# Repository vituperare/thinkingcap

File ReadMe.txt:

The Thinking Cap v1.0 is the first major release of Grindhouse Wet Wares' implementation of the 
tDCS (transcranial Direct Current Stimulation and CES (Cranial Electrotherapy Stimulation)
concepts.  The idea is to stimulate your brain with direct current (in the case of tDCS)
or with square waves of current (in the case of CES) which can either raise or lower the
potential energy of the stimulated neurons, depending on the orientation of electrodes.
This allows them to fire more or less easily, and activates or deactivates a given region,
thus engaging certain brain states.

The code (included) is programmed to control an Arduino-compatible microcontroller to deliver
the necessary current.  It comes in the form of a library, so the hacker can choose his way of
controlling the current.  To create an instantiation of the ThinkingCap class, simply call the
"ThinkingCap" constructor, and then call the methods corresponding to the desired action.

The tDCS setting uses a current source and PWM to ramp up the current at the beginning, and ramp
it back down after a given stimulation time (20 minutes by default, but this setting is also
changeable).  The CES setting pulls a constant square wave, with a frequency to be set by the
user.

If the component values from the schematic are used, the current pulled should be roughly 0.5 mA
or less, but by changing these values, the current level can be manipulated.  However, pulling
currents in excess of 2 mA is not recommended for any use.

The "software" folder contains the software necessary to control the Thinking Cap.  This consists
in an Arduino library called "thinkingcap" and a sample Arduino sketch called "TCexample.ino" that
imports this library.  The example code is designed to apply CES or tDCS depending on the position
of a switch, and to begin when a push-button is activated.

THe "hardware" folder contains gerber files, a bill of materials, and Eagle files necessary to create
a PCB for the Thinking Cap.  This is included within the "thinkingcap10a" folder; the "thinkingcap10b"
folder contains a design for a separate circuit that is not released nor recommended for use.

Thinking Cap v1.0 designed by ianmathwiz7; released 7-1-2013 by Grindhouse Wetware..

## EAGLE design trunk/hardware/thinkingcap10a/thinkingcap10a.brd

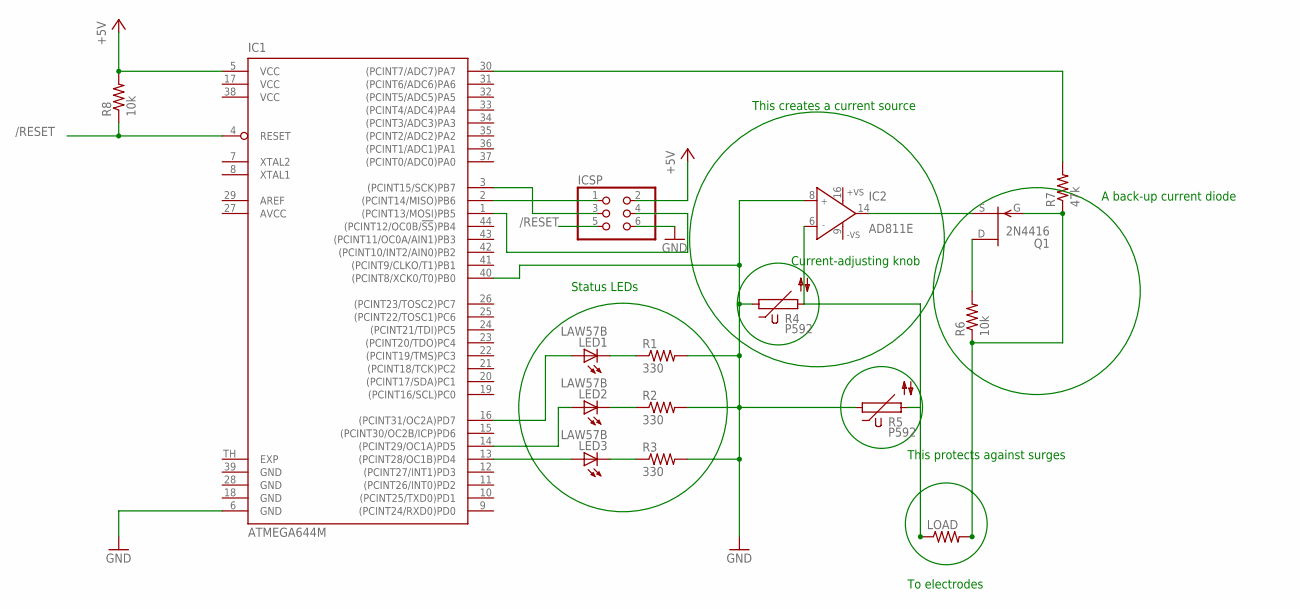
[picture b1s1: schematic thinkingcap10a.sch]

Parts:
IC1: ATMEGA644M; MLF44-TH
IC2: AD811E; PLCC20
ICSP: PINHD-2X3/90; 2X03/90
LED1, LED2, LED3: LAW57B; W57B
LOAD: R-US_0204/2V; 0204V
Q1: 2N4416; TO72
R1, R2, R3: 330; 0204V
R4, R5: P592
R6, R8: 10k; 0204V
R7: 47k; 0204V

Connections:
+5V: IC1.5 (VCC), ICSP.2, R8.2
/RESET: IC1.4 (RESET), ICSP.5, R8.1
AVCC: IC1.27 (AVCC)
EXP: IC1.TH (EXP)
GND: IC1.6 (GND), IC1.18 (GND), IC1.28 (GND), IC1.39 (GND), IC1.40 ((PCINT8/XCK0/T0)PB0), IC2.8 (IN+), ICSP.6, R1.2, R2.2, R3.2
unnamed: IC1.13 ((PCINT28/OC1B)PD4), LED3.A
unnamed: IC1.14 ((PCINT29/OC1A)PD5), LED2.A
unnamed: IC1.16 ((PCINT31/OC2A)PD7), LED1.A
unnamed: LED1.C, LED1.C@1 (C), LED1.C@2 (C), LED1.C@3 (C), LED1.C@4 (C), LED1.C@5 (C), R1.1
unnamed: LED2.C, LED2.C@1 (C), LED2.C@2 (C), LED2.C@3 (C), LED2.C@4 (C), LED2.C@5 (C), R2.1
unnamed: LED3.C, LED3.C@1 (C), LED3.C@2 (C), LED3.C@3 (C), LED3.C@4 (C), LED3.C@5 (C), R3.1
unnamed: IC1.2 ((PCINT14/MISO)PB6), ICSP.1
unnamed: IC2.6 (IN-), LOAD.1
unnamed: IC2.14 (OUT), Q1.1 (S)
unnamed: Q1.2 (D), R6.2
unnamed: IC1.30 ((PCINT7/ADC7)PA7), R7.2
unnamed: LOAD.2, Q1.3 (G), R6.1, R7.1
unnamed: IC1.3 ((PCINT15/SCK)PB7), ICSP.3
unnamed: IC1.1 ((PCINT13/MOSI)PB5), ICSP.4
VCC: IC1.17 (VCC), IC1.38 (VCC)

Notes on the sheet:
To electrodes
Status LEDs
This creates a current source
Current-adjusting knob
This protects against surges
A back-up current diode

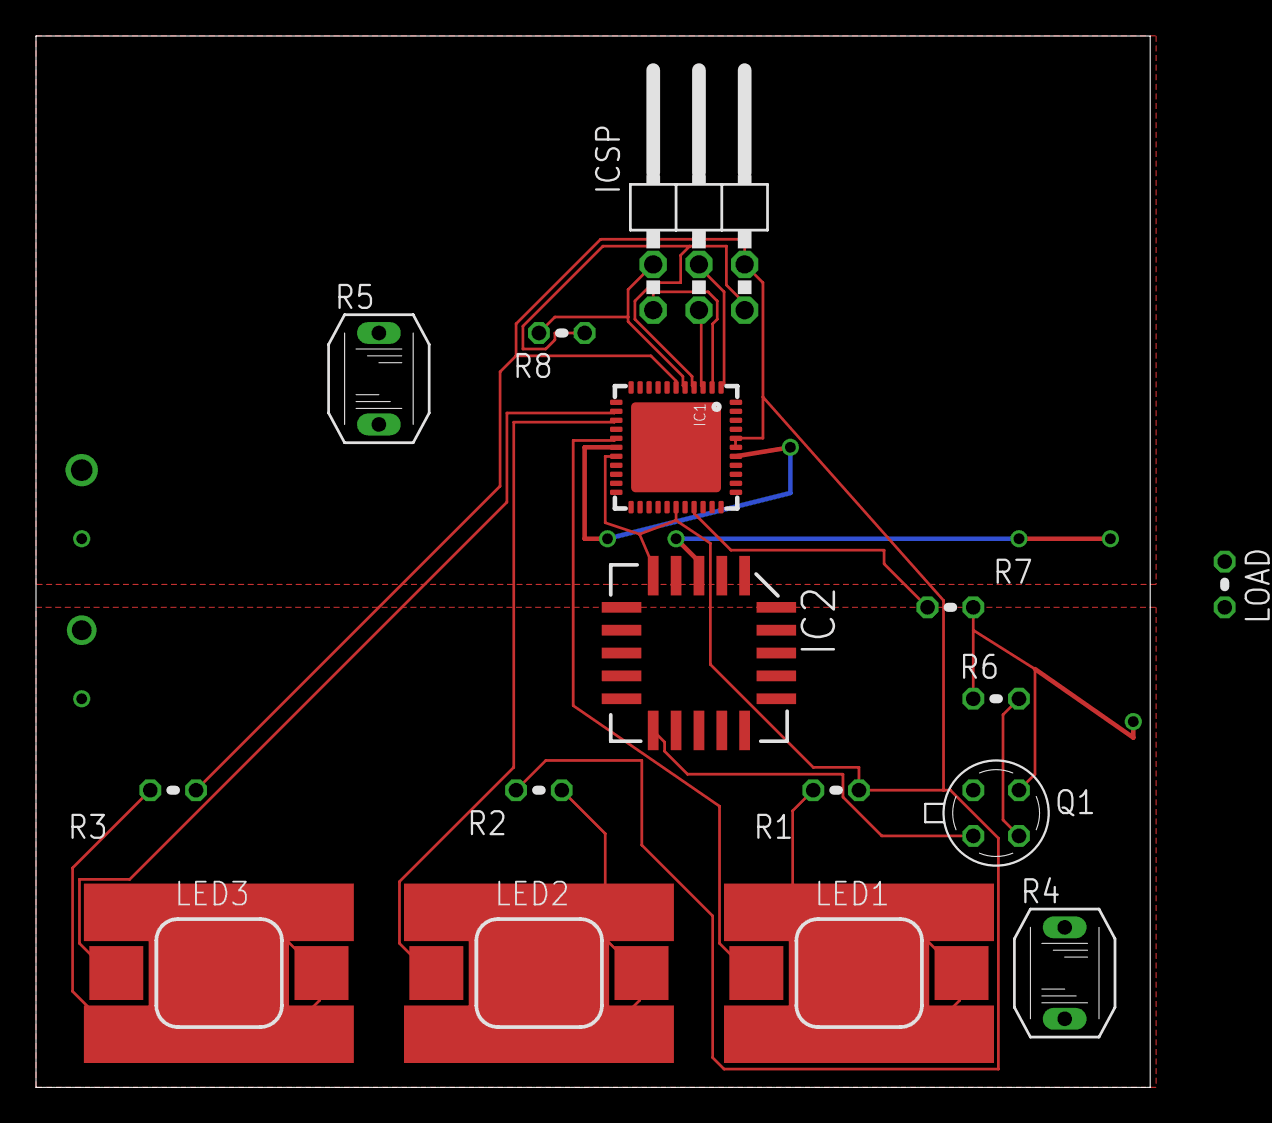
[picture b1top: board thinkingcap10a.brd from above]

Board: 2 copper layers, 61.9 x 58.4 mm, 16 parts (0 on the bottom side), 18 nets.

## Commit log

2012-06-02 Initial directory structure.
2012-08-19 Checking initial thinking_cap code
2012-08-26 I am modifying this to illustrate svn
2012-08-26 Removing debug code, because it shouldn't be there.
2012-08-27 Here is the current thinkingcap library, modified to accommodate Tim's suggestions, and also to make it run more cleanly.
2012-11-23 Added CES functionality; disabled the tMS code; cleaned up the code slightly
2012-11-24 Added schematics (both the external release and the tMS prototype for internal release) and README file; performed final cleanup; v1.0 is officially ready for release!
2012-12-02 Added schematics and README for realz this time, because subversion is too lazy to do it automatically.
2012-12-09 Added example code
2013-03-04 Created wiki page through web user interface.
2013-03-04 Edited wiki page thinkingcap through web user interface.
2013-05-24 Updated SCH (a) to v1.0
2013-06-14 Created PCB files; final draft for v1.0
2015-05-11 Migrating wiki contents from Google Code
